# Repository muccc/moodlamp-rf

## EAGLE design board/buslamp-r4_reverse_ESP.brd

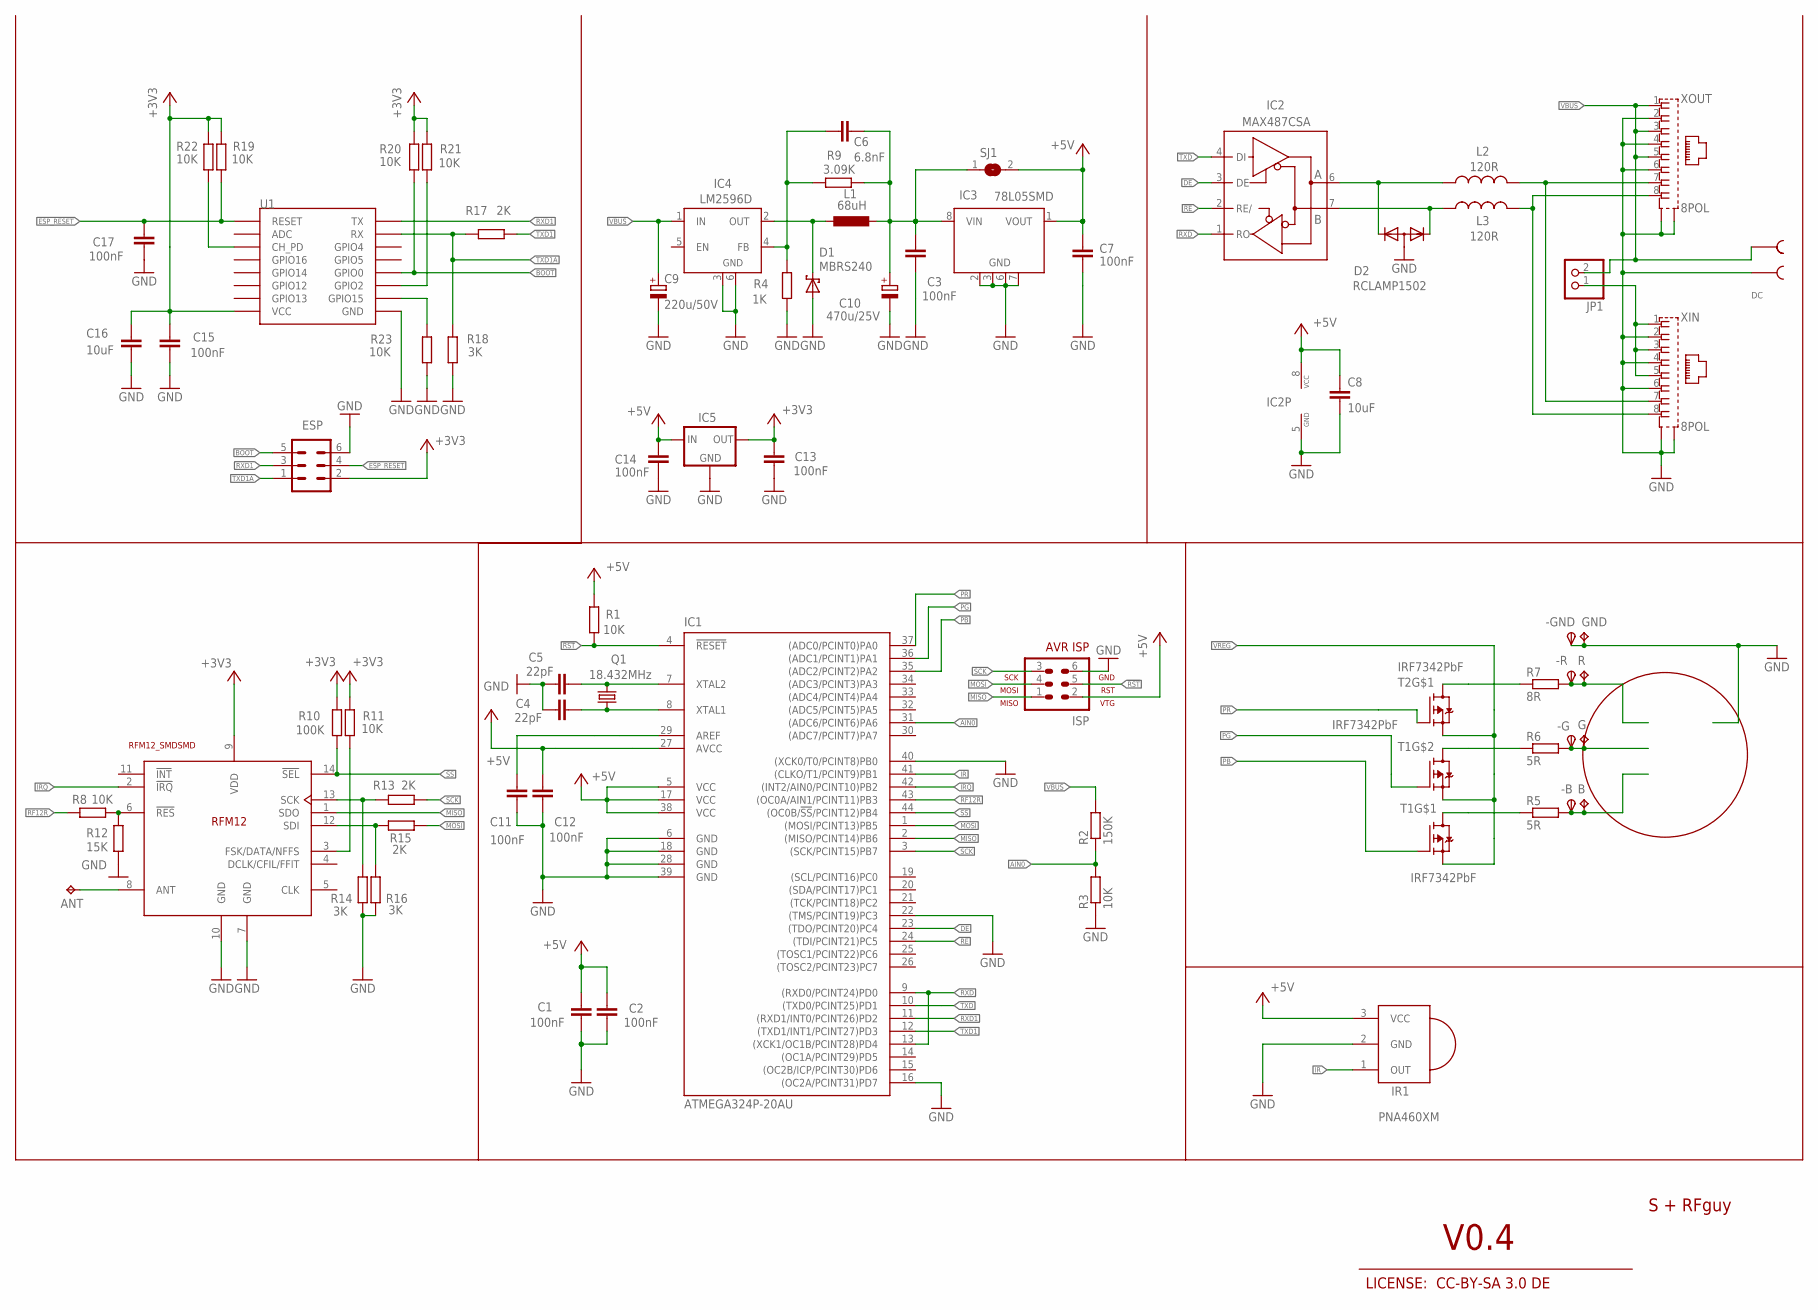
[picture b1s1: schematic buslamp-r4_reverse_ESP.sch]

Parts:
-B: TPSTP212R; TP212R
-G: TPSTP212R; TP212R
-GND: TPSTP212R; TP212R
-R: TPSTP212R; TP212R
ANT: TPPAD1-13; P1-13
B: TPPAD1-13; P1-13
C1, C2, C3, C7: 100nF; C0805K
C4, C5: 22pF; C0805K
C6: 6.8nF; C0805K
C8, C16: 10uF; C1210
C9: 220u/50V; UD-10X10_NICHICON
C10: 470u/25V; UD-10X10_NICHICON
C11, C12, C13, C14, C15, C17: 100nF; C0805
D1: MBRS240; SMB
D2: RCLAMP1502; SOT23
DC: STL-266-2
ESP: MA03-2
G: TPPAD1-13; P1-13
GND: TPPAD1-13; P1-13
IC1: ATMEGA324P-20AU; TQFP44
IC2: MAX487CSA; SO08
IC3: 78L05SMD; SO08
IC4: LM2596D; TO263-5
IC5: MCP1700SOT23; SOT23
IR1: PNA460XM
ISP: AVR-ISP-6
JP1: PINHD-1X2; 1X02
L1: 68uH; PIS4728
L2, L3: 120R; L0603
Q1: 18.432MHz; HC49/S
R: TPPAD1-13; P1-13
R1, R8, R11, R19, R20, R21, R22, R23: 10K; M0805
R2: 150K; R0805
R3: 10K; R0805
R4: 1K; M0805
R5, R6: 5R; 0617/17
R7: 8R; 0617/17
R9: 3.09K; M0805
R10: 100K; M0805
R12: 15K; M0805
R13, R15, R17: 2K; M0805
R14, R16, R18: 3K; M0805
RF1: RFM12_SMDSMD; RFM12
SJ1: SJ
T1, T2: IRF7342PbF; SO08-IRF
U1: ESP12SMD; ESP12-SMD
U$2: KK-STERN; STERN
XIN: 8POL
XOUT: 8POL

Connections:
!RE: IC1.24 ((TDI/PCINT21)PC5), IC2.2 (RE/)
!RST: IC1.4 (!RESET), ISP.5, R1.1
+3V3: C13.2, C15.2, C16.1, ESP.2, IC5.2 (OUT), R10.1, R11.1, R19.1, R20.1, R21.1, R22.1, RF1.9 (VDD), U1.VCC
+5V: C1.1, C2.1, C7.1, C8.1, C12.2, C14.2, IC1.5 (VCC), IC1.17 (VCC), IC1.27 (AVCC), IC1.38 (VCC), IC2.8 (VCC), IC3.1 (VOUT), IC5.3 (IN), IR1.3 (VCC), ISP.2, R1.2, SJ1.2
A: L2.2, XIN.7, XOUT.7
AIN0: IC1.31 ((ADC6/PCINT6)PA6), R2.1, R3.2
B: L3.2, XIN.8, XOUT.8
BOOT: ESP.5, R20.2, U1.GPIO0
DE: IC1.23 ((TDO/PCINT20)PC4), IC2.3 (DE)
ESP_RESET: C17.2, ESP.4, R19.2, U1.RESET
G: -G.TP, G.TP, R6.2
GND: -GND.TP, C1.2, C2.2, C3.2, C4.1, C5.1, C7.2, C8.2, C9.-, C10.-, C11.1, C12.1, C13.1, C14.1, C15.1, C16.2, C17.1, D1.A, D2.3 (A), DC.P$3, ESP.6, GND.TP, IC1.6 (GND), IC1.16 ((OC2A/PCINT31)PD7), IC1.18 (GND), IC1.22 ((TMS/PCINT19)PC3), IC1.28 (GND), IC1.39 (GND), IC1.40 ((XCK0/T0/PCINT8)PB0), IC2.5 (GND), IC3.2 (GND), IC3.3 (GND), IC3.6 (GND), IC3.7 (GND), IC4.3 (GND), IC4.6 (GND), IC5.1 (GND), IR1.2 (GND), ISP.6, R3.1, R4.2, R12.2, R14.2, R16.2, R18.2, R23.2, RF1.7 (GND), RF1.10 (GND), U1.GND, XIN.2, XIN.4, XIN.6, XIN.S1, XIN.S2, XOUT.2, XOUT.4, XOUT.6, XOUT.S1, XOUT.S2
IR: IC1.41 ((CLKO/T1/PCINT9)PB1), IR1.1 (OUT)
IRQ: IC1.42 ((INT2/AIN0/PCINT10)PB2), RF1.2 (!IRQ)
MISO: IC1.2 ((MISO/PCINT14)PB6), ISP.1, RF1.1 (SDO)
MOSI: IC1.1 ((MOSI/PCINT13)PB5), ISP.4, R15.2
unnamed: R7.1, T2.7 (D), T2.8 (D)
unnamed: R8.2, R12.1, RF1.6 (!RES)
unnamed: C6.1, IC4.4 (FB), R4.1, R9.2
unnamed: R6.1, T1.5 (D), T1.6 (D)
unnamed: R5.1, T1.7 (D), T1.8 (D)
unnamed: -B.TP, B.TP, R5.2
unnamed: R13.1, R14.1, RF1.13 (SCK)
unnamed: R15.1, R16.1, RF1.12 (SDI)
unnamed: ANT.TP, RF1.8 (ANT)
unnamed: D1.C, IC4.2 (OUT), L1.1
unnamed: D2.2 (K2), IC2.6 (A), L2.1
unnamed: D2.1 (K1), IC2.7 (B), L3.1
unnamed: R11.2, RF1.3 (FSK/DATA/NFFS)
unnamed: R21.2, U1.GPIO2
unnamed: R22.2, U1.CH_PD
unnamed: R23.1, U1.GPIO15
unnamed: C11.2, IC1.29 (AREF)
PB: IC1.35 ((ADC2/PCINT2)PA2), T1.2 (G)
PG: IC1.36 ((ADC1/PCINT1)PA1), T1.4 (G)
PR: IC1.37 ((ADC0/PCINT0)PA0), T2.2 (G)
R: -R.TP, R.TP, R7.2
RF12R: IC1.43 ((OC0A/AIN1/PCINT11)PB3), R8.1
RXD: IC1.9 ((RXD0/PCINT24)PD0), IC1.13 ((XCK1/OC1B/PCINT28)PD4), IC2.1 (RO)
RXD1: ESP.3, IC1.11 ((RXD1/INT0/PCINT26)PD2), U1.TXD0 (TX)
SCK: IC1.3 ((SCK/PCINT15)PB7), ISP.3, R13.2
SS: IC1.44 ((OC0B/!SS!/PCINT12)PB4), R10.2, RF1.14 (!SEL)
TXD: IC1.10 ((TXD0/PCINT25)PD1), IC2.4 (DI)
TXD1: IC1.12 ((TXD1/INT1/PCINT27)PD3), R17.2
TXD1A: ESP.1, R17.1, R18.1, U1.RXD0 (RX)
VBUS: C9.+, DC.P$4, IC4.1 (IN), JP1.2, R2.2, XOUT.1, XOUT.3, XOUT.5
VBUSOUT: JP1.1, XIN.1, XIN.3, XIN.5
VREG: C3.1, C6.2, C10.+, IC3.8 (VIN), L1.2, R9.1, SJ1.1, T1.1 (S), T1.3 (S), T2.1 (S)
XTAL1: C5.2, IC1.7 (XTAL2), Q1.2
XTAL2: C4.2, IC1.8 (XTAL1), Q1.1

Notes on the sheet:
S + RFguy
V0.4
LICENSE: CC-BY-SA 3.0 DE

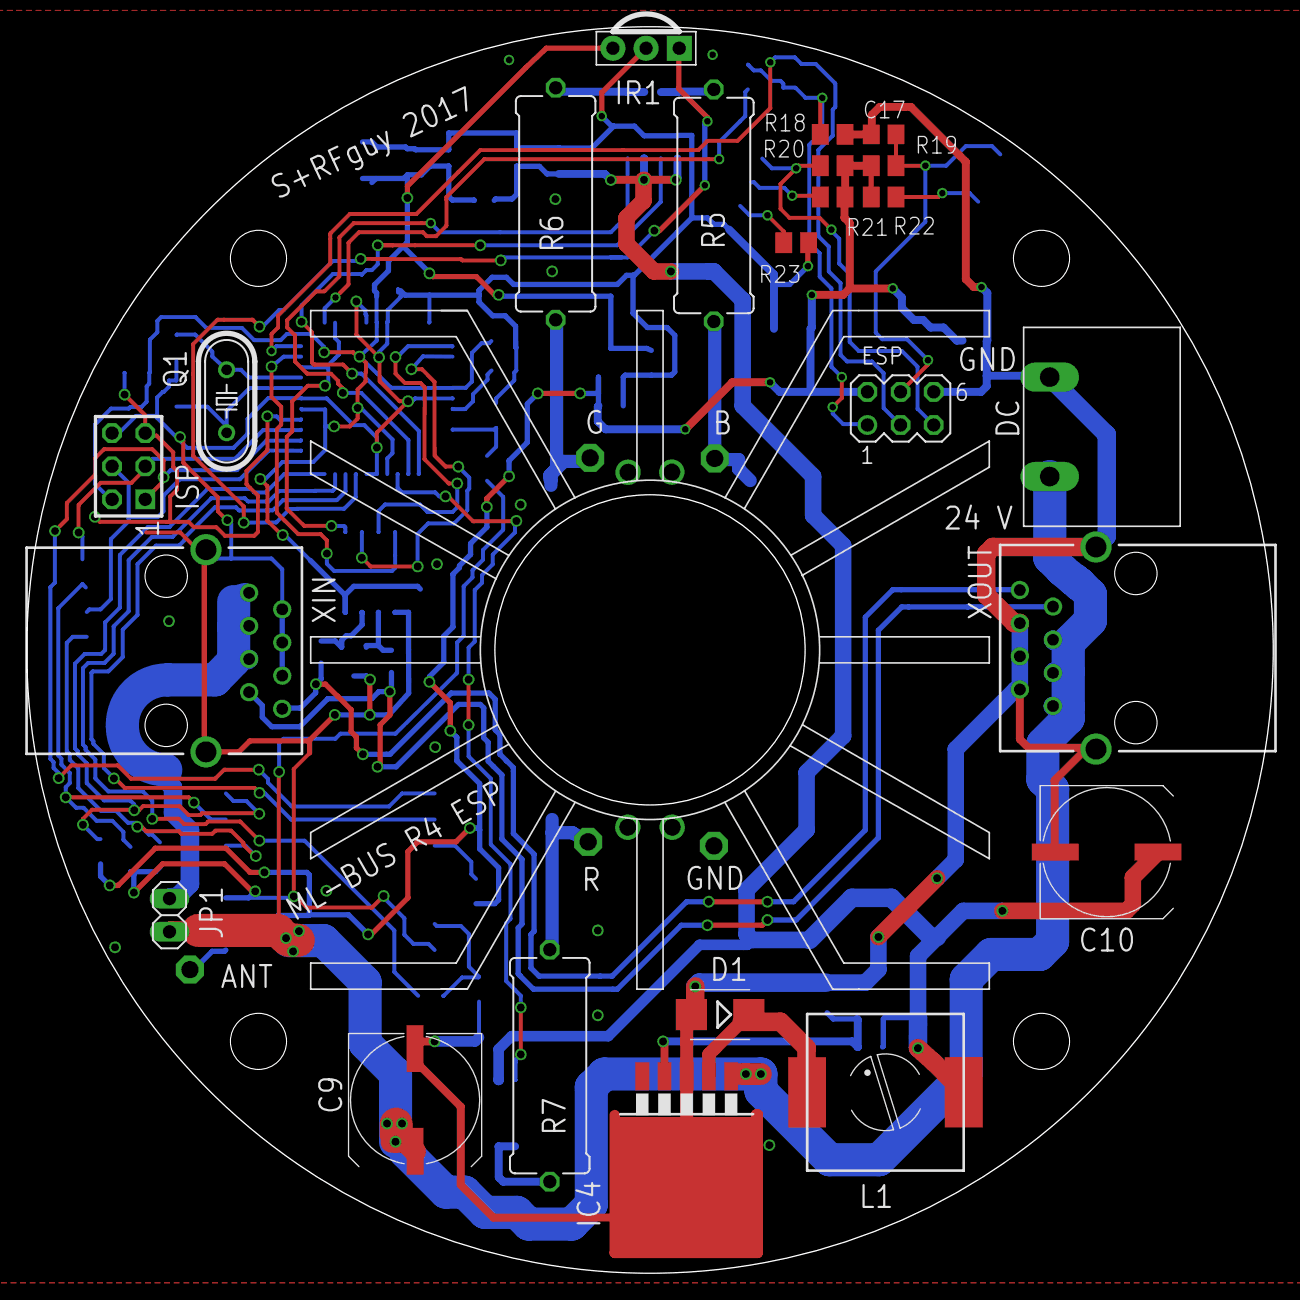
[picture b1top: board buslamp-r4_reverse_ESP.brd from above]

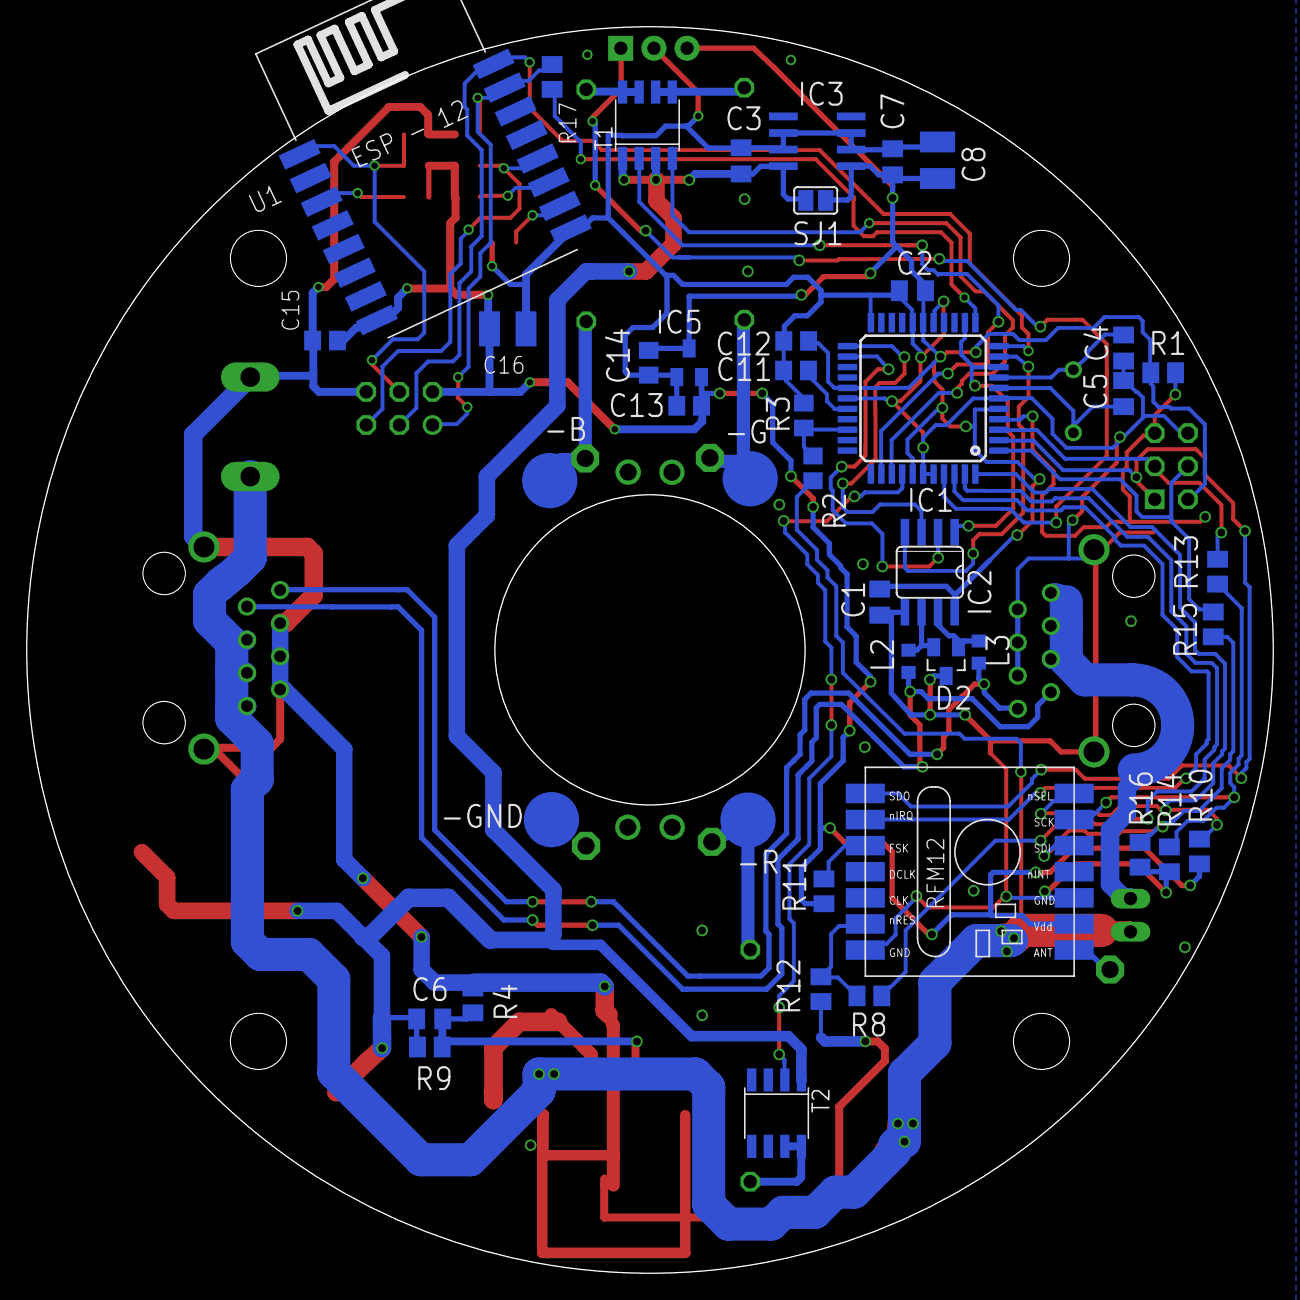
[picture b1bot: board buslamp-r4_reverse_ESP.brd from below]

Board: 2 copper layers, 95.5 x 95.5 mm, 73 parts (44 on the bottom side), 50 nets.

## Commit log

2016-01-20 Reverse Variante für DX Leds
2017-02-21 Bus MoodLamp R4 for Reverse DX LED with P-Kanal FET and ESP8266-12 WLAN Bridge, Schematic cleanup, 100 pieces ordered by seeed today
